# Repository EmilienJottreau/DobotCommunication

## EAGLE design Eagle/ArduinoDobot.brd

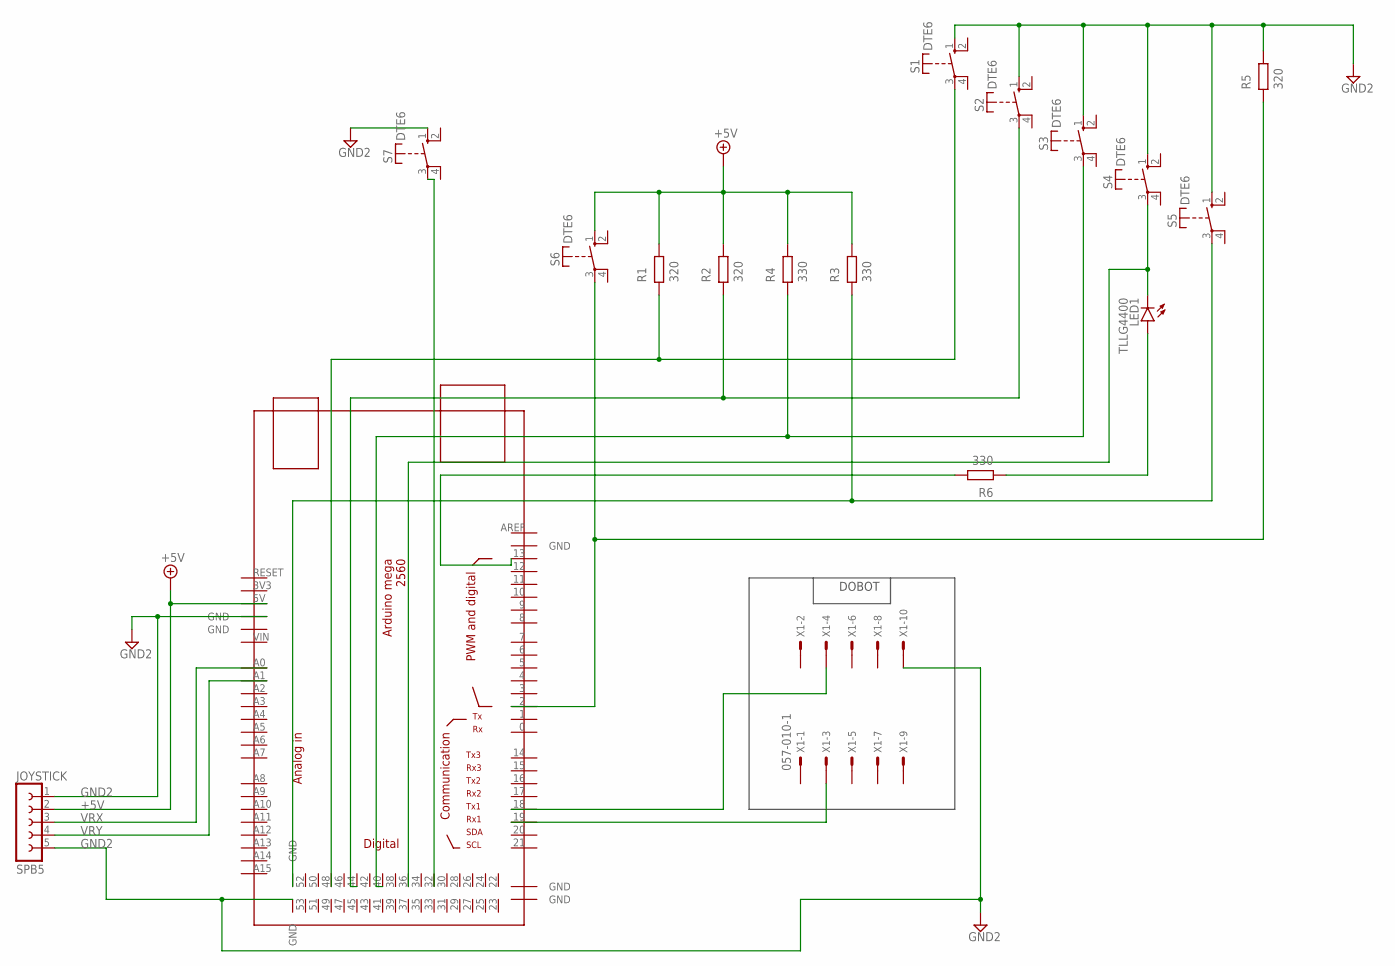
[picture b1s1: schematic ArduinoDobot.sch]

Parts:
JOYSTICK: SPB5
LED1: TLLG4400; LED3MM
S1, S2, S3, S4, S5, S6, S7: DTE6
U$1: MEGA_DEVICE; MEGAOUTLINE
X1: 057-010-1

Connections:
+5V: JOYSTICK.2, S6.1 (S), U$1.5V
GND2: JOYSTICK.1, JOYSTICK.5, S1.1 (S), S2.1 (S), S3.1 (S), S4.1 (S), S5.1 (S), S7.1 (S), U$1.GND@2 (GND), U$1.GND@7 (GND), X1.10
unnamed: S1.3, U$1.48
unnamed: S7.3, U$1.32
unnamed: U$1.19, X1.3
unnamed: U$1.18, X1.4
unnamed: S2.3, U$1.44
unnamed: S6.3, U$1.2
unnamed: S3.3, U$1.40
unnamed: S5.3, U$1.GND@6 (GND)
unnamed: LED1.K (C), S4.3, U$1.36
VRX: JOYSTICK.3, U$1.A0
VRY: JOYSTICK.4, U$1.A1

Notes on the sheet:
DOBOT

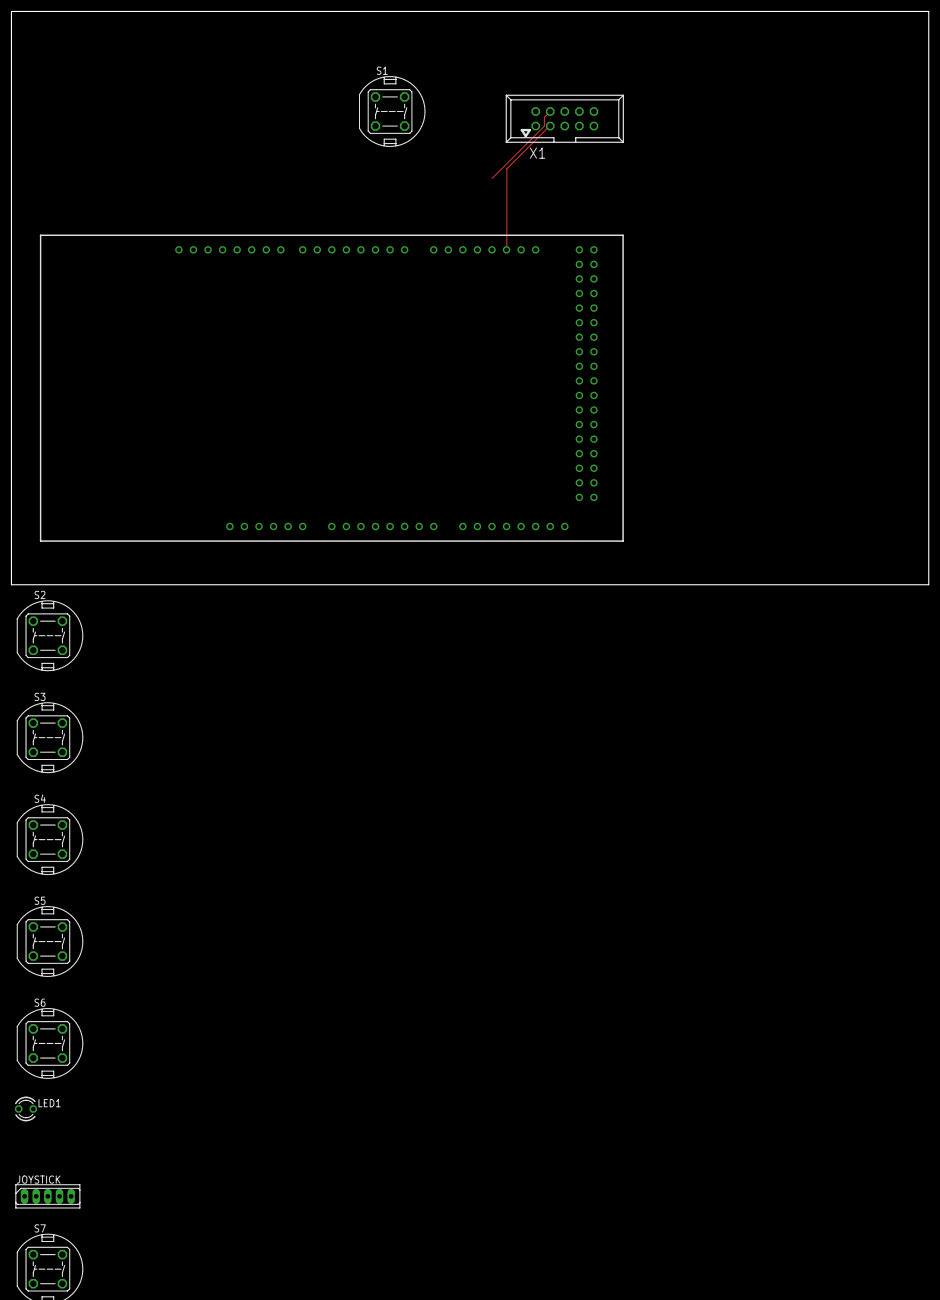
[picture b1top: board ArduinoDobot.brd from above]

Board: 2 copper layers, 160.0 x 100.0 mm, 11 parts (0 on the bottom side), 13 nets.

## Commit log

2023-02-08 clear dir
2023-02-08 Ajout de Codes.txt
    Ajout du fichier txt résumant les ID de différentes fonctions du robot
2023-02-08 TrameInterpret added
2023-02-08 fonctionsTrames added (to replace InterpretTrames)
2023-02-08 fonctionsTrames added (to replace TramesInterpret)
2023-02-08 fin de seance 08/02, working two dobots
2023-02-11 added joystick control
2023-02-15 Eagle files added
    Schematic, board and ArduinoMega librairy added
2023-02-15 Start/Stop, Emergency Stop, Change print monitor
2023-02-15 renamed files, schematic updated
    untitled -> ArduinoDobot.
    Schematic updated
2023-02-15 InterpretMessage implemented in ProtocolProcess()
2023-03-15 ordo created
2023-03-15 ordo created on dobot.h
2023-03-15 demo button added
2023-03-18 ajout des g codes
2023-03-18 g code instruction avec next
2023-03-22 version temporaire pour tester le nextInstruction
2023-03-22 getPos(), initPos(), etc... added
2023-03-22 getPos(), initPos(), etc... and gCode parser added
2023-03-22 Command.h structs fixed
2023-03-22 structs fixed
2023-03-22 dobots array pointers fixed
2023-03-22 New files added and Emilien's files included
2023-03-22 Dobot.h added
2023-04-05 code fonctionnel pour les trois robots
2023-04-09 fin de seance
2023-04-10 fix nb_new_instruction
2023-04-11 version optimisée en ram
2023-04-16 derniere version jeudi 13/04
2023-04-17 world -> word
2023-04-21 clean repo
